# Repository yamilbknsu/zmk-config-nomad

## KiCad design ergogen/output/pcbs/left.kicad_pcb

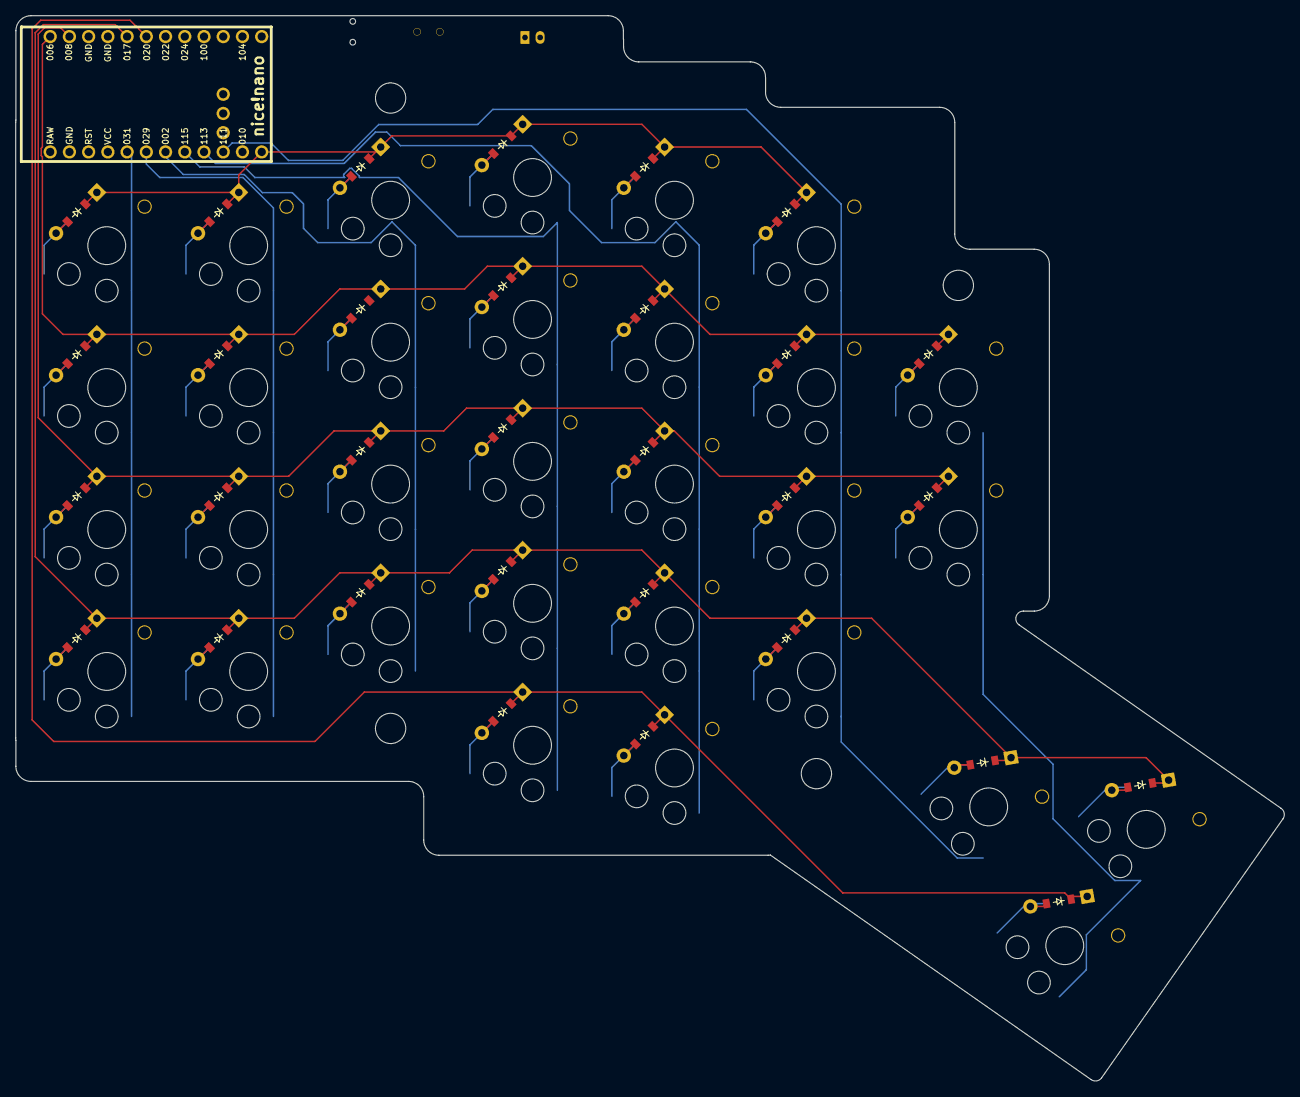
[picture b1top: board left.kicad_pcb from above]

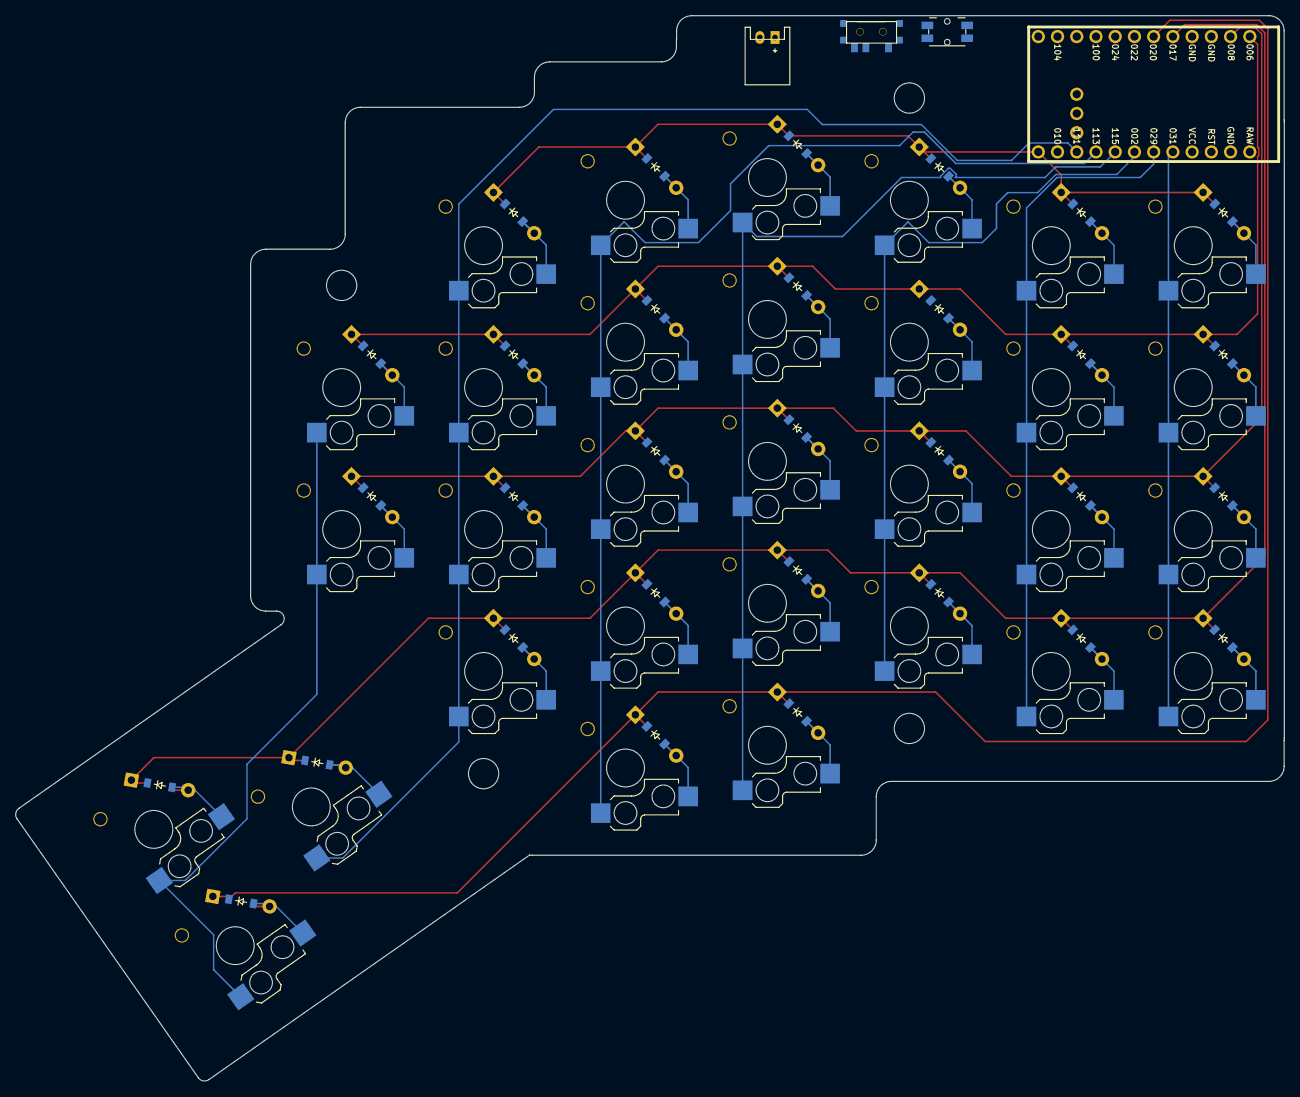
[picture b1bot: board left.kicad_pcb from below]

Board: 2 copper layers, 167.6 x 140.7 mm, 66 parts (31 on the bottom side), 47 nets.

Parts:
B1: Panasonic_EVQPUL_EVQPUC
D1, D2, D3, D4, D5, D6, D7, D8, D9, D10, D11, D12, D13, D14, D15, D16, D17, D18, D19, D20, D21, D22, D23, D24, D25, D26, D27, D28, D29, D30, D31: ComboDiode
JST1: JST_PH_S2B-PH-K_02x2.00mm_Angled
MCU1: nice_nano
S1, S2, S3, S4, S5, S6, S7, S8, S9, S10, S11, S12, S13, S14, S15, S16, S17, S18, S19, S20, S21, S22, S23, S24, S25, S26, S27, S28, S29, S30, S31: switch_choc_v1_v2
T1: SPDT_C128955

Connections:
GND: B1.1, JST1.2, MCU1.3, MCU1.4, MCU1.23
P002: MCU1.18, S9.1, S10.1, S11.1, S12.1
P006: D3.1, D7.1, D11.1, D16.1, D21.1, D25.1, D28.1, MCU1.1
P008: D2.1, D6.1, D10.1, D15.1, D20.1, D24.1, D27.1, MCU1.2
P009: D4.1, D8.1, D12.1, D17.1, D22.1, D26.1, MCU1.13
P010: MCU1.14, S27.1, S28.1, S30.1, S31.1
P017: D1.1, D5.1, D9.1, D14.1, D19.1, D23.1, D29.1, D31.1, MCU1.5
P020: D13.1, D18.1, D30.1, MCU1.6
P029: MCU1.19, S5.1, S6.1, S7.1, S8.1
P031: MCU1.20, S1.1, S2.1, S3.1, S4.1
P111: MCU1.15, S23.1, S24.1, S25.1, S26.1, S29.1
P113: MCU1.16, S18.1, S19.1, S20.1, S21.1, S22.1
P115: MCU1.17, S13.1, S14.1, S15.1, S16.1, S17.1
RAW: MCU1.24, T1.2
RST: B1.2, MCU1.22
actions_bottom: D1.2, S1.2
actions_home: D2.2, S2.2
actions_numbers: D4.2, S4.2
actions_top: D3.2, S3.2
forward_thumb: D31.2, S31.2
forward_top: D30.2, S30.2
index_bottom: D19.2, S19.2
index_home: D20.2, S20.2
index_modifiers: D18.2, S18.2
index_numbers: D22.2, S22.2
index_top: D21.2, S21.2
inner_bottom: D23.2, S23.2
inner_home: D24.2, S24.2
inner_numbers: D26.2, S26.2
inner_top: D25.2, S25.2
middle_bottom: D14.2, S14.2
middle_home: D15.2, S15.2
middle_modifiers: D13.2, S13.2
middle_numbers: D17.2, S17.2
middle_top: D16.2, S16.2
pinky_bottom: D5.2, S5.2
pinky_home: D6.2, S6.2
pinky_numbers: D8.2, S8.2
pinky_top: D7.2, S7.2
pos: JST1.1, T1.1
ring_bottom: D9.2, S9.2
ring_home: D10.2, S10.2
ring_numbers: D12.2, S12.2
ring_top: D11.2, S11.2
space_thumb: D29.2, S29.2
special_home: D27.2, S27.2
special_top: D28.2, S28.2

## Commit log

2026-03-22 fix `module.yml`
2026-03-22 move yml files
2026-03-22 renamed yaml
2026-03-22 changed zmk revision
2026-03-22 reverted revision, changed to `nice_nano`
2026-03-22 keymap fixes
2026-03-22 `DQT` for `DOUBLEQUOTE`
2026-03-22 added `zmk`
2026-03-27 keymap
2026-04-24 update keymap
2026-04-24 fix keymap
2026-04-24 alternative keymap
2026-04-28 updated keymap
